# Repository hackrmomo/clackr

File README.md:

# Clackr: A fresh new ergo column staggered keyboard

Todo:
- [x] Populate points in config.yaml
- [x] Populate outlines in config.yaml
- [x] Populate pcbs in config.yaml
- [ ] Populate cases in config.yaml
- [ ] Design high-end case with polished brass bottom
- [ ] Add mounting holes to PCBs and plates
- [ ] Add images
- [ ] Add build guide
- [ ] Add firmware
- [ ] Add ZMK keymaps
- [x] Build gerbers
- [x] Build BOM (https://docs.google.com/spreadsheets/d/1K3NJizndCrkzU6wi76FKWawuainESK8DETb3sXQge9k/edit?usp=sharing)

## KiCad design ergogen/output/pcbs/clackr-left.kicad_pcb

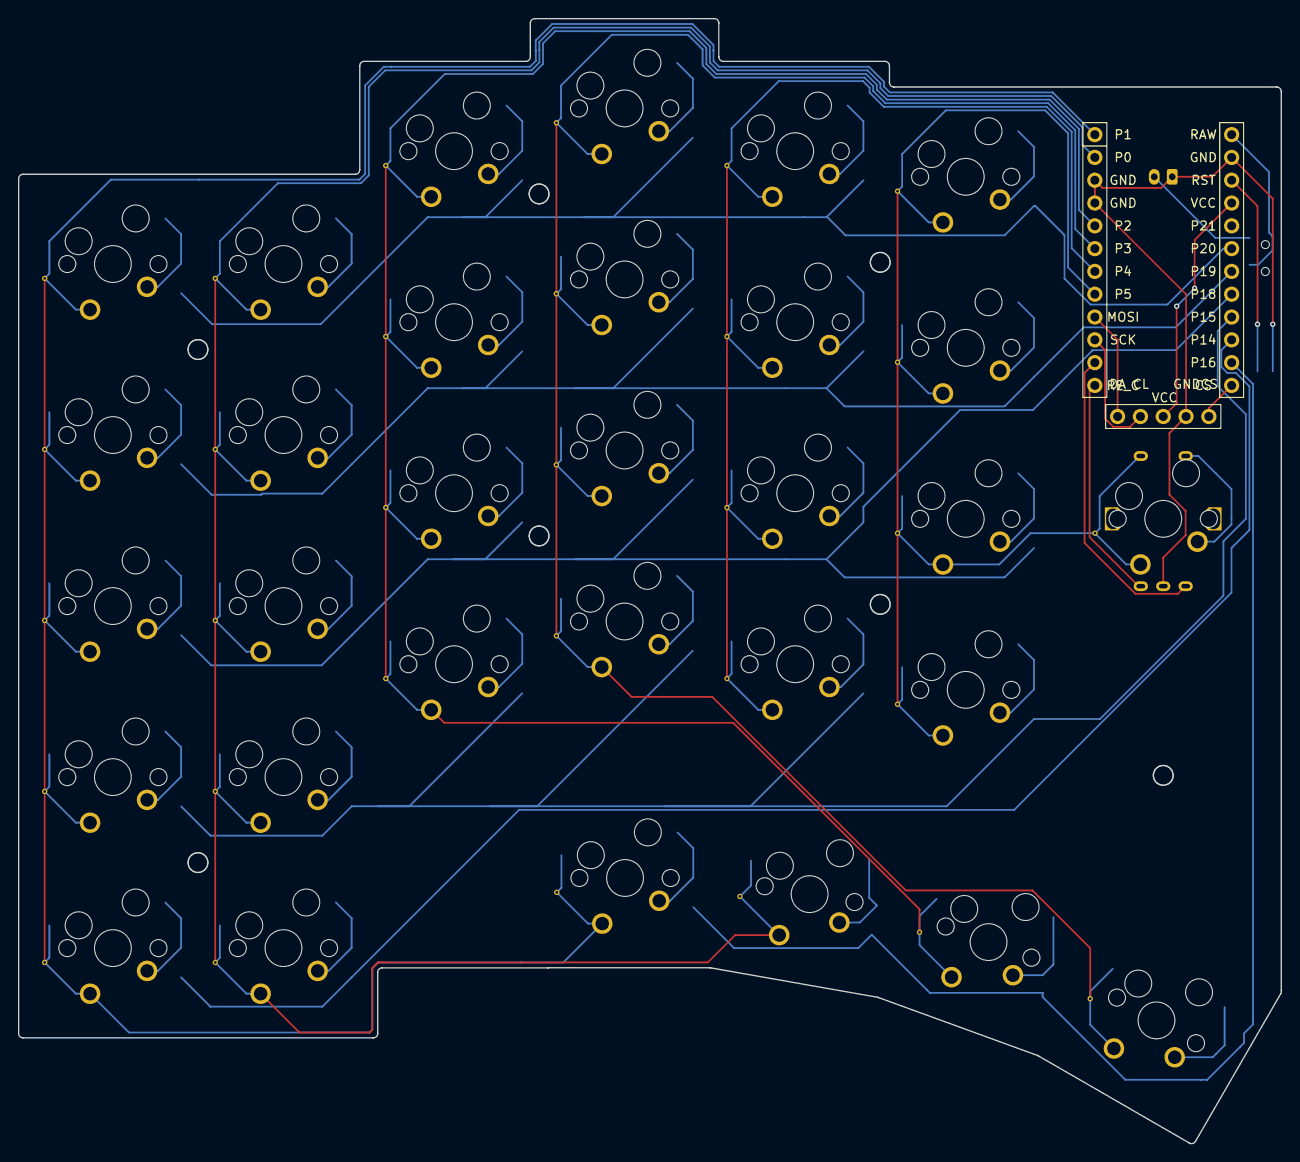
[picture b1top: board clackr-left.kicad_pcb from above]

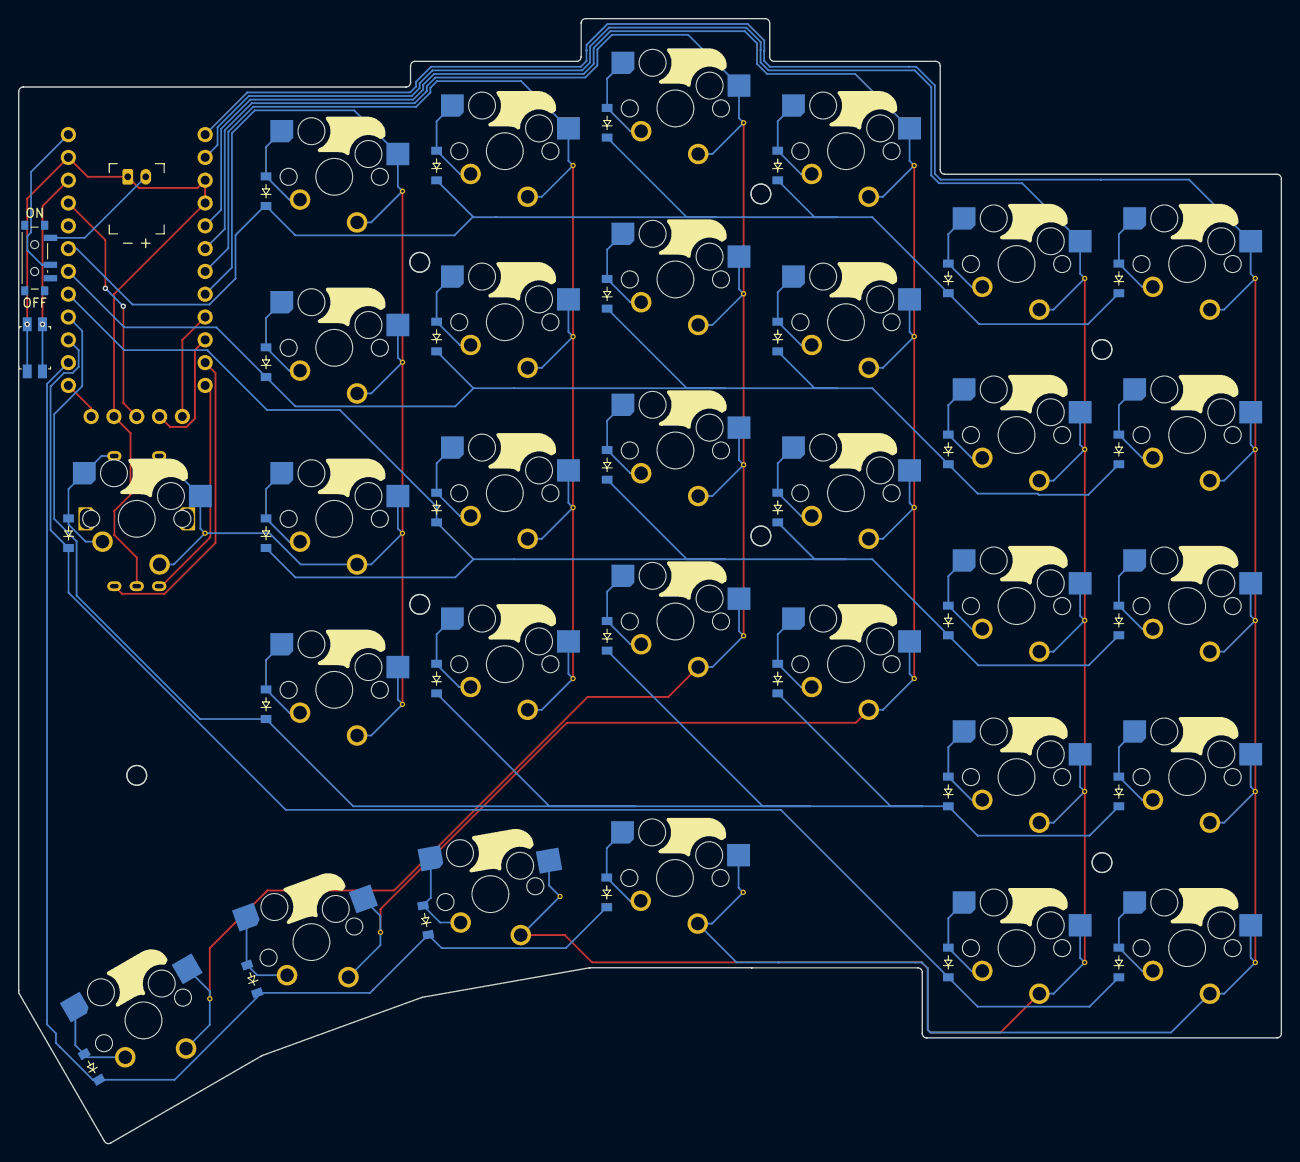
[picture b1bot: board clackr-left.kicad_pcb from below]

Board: 2 copper layers, 140.7 x 125.3 mm, 75 parts (65 on the bottom side), 53 nets.

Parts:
D1, D2, D3, D4, D5, D6, D7, D8, D9, D10, D11, D12, D13, D14, D15, D16, D17, D18, D19, D20, D21, D22, D23, D24, D25, D26, D27, D28, D29, D30, D31: diode_tht_sod123
DISP1: display_nice_view
JST1: battery_connector_jst_ph_2
MCU1: mcu_nice_nano
MH1, MH2, MH3, MH4, MH5, MH6, MH7: mounting_hole_npth
PWR1: power_switch_smd_side
RE1: rotary_encoder_ec11_ec12
RST1: reset_switch_smd_side
S1, S2, S3, S4, S5, S6, S7, S8, S9, S10, S11, S12, S13, S14, S15, S16, S17, S18, S19, S20, S21, S22, S23, S24, S25, S26, S27, S28, S29, S30, S31: switch_mx

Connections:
BAT_P: JST1.2, PWR1.1
CS: DISP1.5, MCU1.12
GND: DISP1.4, JST1.1, MCU1.2, MCU1.21, MCU1.22, RE1.B, RST1.1, RST1.3
MOSI: DISP1.1, MCU1.16
P0: MCU1.23, S6.1, S7.1, S8.1, S9.1, S10.1, S28.1
P1: MCU1.24, S1.1, S2.1, S3.1, S4.1, S5.1, S27.1
P2: MCU1.20, S11.1, S12.1, S13.1, S14.1, S29.1
P3: MCU1.19, S15.1, S16.1, S17.1, S18.1, S30.1
P4: MCU1.18, S19.1, S20.1, S21.1, S22.1
P5: MCU1.17, RE1.S1, S23.1, S24.1, S25.1, S26.1, S31.1
P14: D1.1, D6.1, D31.1, MCU1.10
P15: D2.1, D7.1, D11.1, D15.1, D19.1, D23.1, MCU1.9
P16: D27.1, D28.1, D29.1, D30.1, MCU1.11
P18: D3.1, D8.1, D12.1, D16.1, D20.1, D24.1, MCU1.8
P19: D4.1, D9.1, D13.1, D17.1, D21.1, D25.1, MCU1.7
P20: D5.1, D10.1, D14.1, D18.1, D22.1, D26.1, MCU1.6
RAW: MCU1.1, PWR1.2
RE_A: MCU1.14, RE1.A
RE_C: MCU1.13, RE1.C
RST: MCU1.3, RST1.2, RST1.4
SCK: DISP1.2, MCU1.15
VCC: DISP1.3, MCU1.4
encoder_default: D31.2, RE1.S2, S31.2
extra-extra-reachy_default: D30.2, S30.2
extra-reachy_default: D29.2, S29.2
index0_bottom: D19.2, S19.2
index0_home: D20.2, S20.2
index0_numerics: D22.2, S22.2
index0_top: D21.2, S21.2
index1_bottom: D23.2, S23.2
index1_home: D24.2, S24.2
index1_numerics: D26.2, S26.2
index1_top: D25.2, S25.2
middle_bottom: D15.2, S15.2
middle_home: D16.2, S16.2
middle_numerics: D18.2, S18.2
middle_top: D17.2, S17.2
pinky0_bottom: D2.2, S2.2
pinky0_home: D3.2, S3.2
pinky0_modifiers: D1.2, S1.2
pinky0_numerics: D5.2, S5.2
pinky0_top: D4.2, S4.2
pinky1_bottom: D7.2, S7.2
pinky1_home: D8.2, S8.2
pinky1_modifiers: D6.2, S6.2
pinky1_numerics: D10.2, S10.2
pinky1_top: D9.2, S9.2
reachy_default: D28.2, S28.2
ring_bottom: D11.2, S11.2
ring_home: D12.2, S12.2
ring_numerics: D14.2, S14.2
ring_top: D13.2, S13.2
tucky_default: D27.2, S27.2

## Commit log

2024-08-11 add @ceoloide footprints
2024-08-11 add a temporary gitignore
2024-08-11 finish keyboard config and routing
2024-08-11 add "finished" files
2024-08-11 reset right side
2024-08-14 temp
2024-09-09 Finalize Config
2024-09-09 update gitignore
2024-09-09 remove old casefiles
2024-09-09 add pcb STEP files
2024-09-09 add case STEP files
2024-09-09 update all outlines
